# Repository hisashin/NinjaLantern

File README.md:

NinjaLantern
==========

Open Source(GPL) Transilluminator to view DNA,RNA,etc.

STL https://github.com/hisashin/NinjaLantern/blob/master/cad/3d/Illuminator_ver2.stl

Photos https://www.facebook.com/hisakawa/media_set?set=a.10151899171609481&type=3

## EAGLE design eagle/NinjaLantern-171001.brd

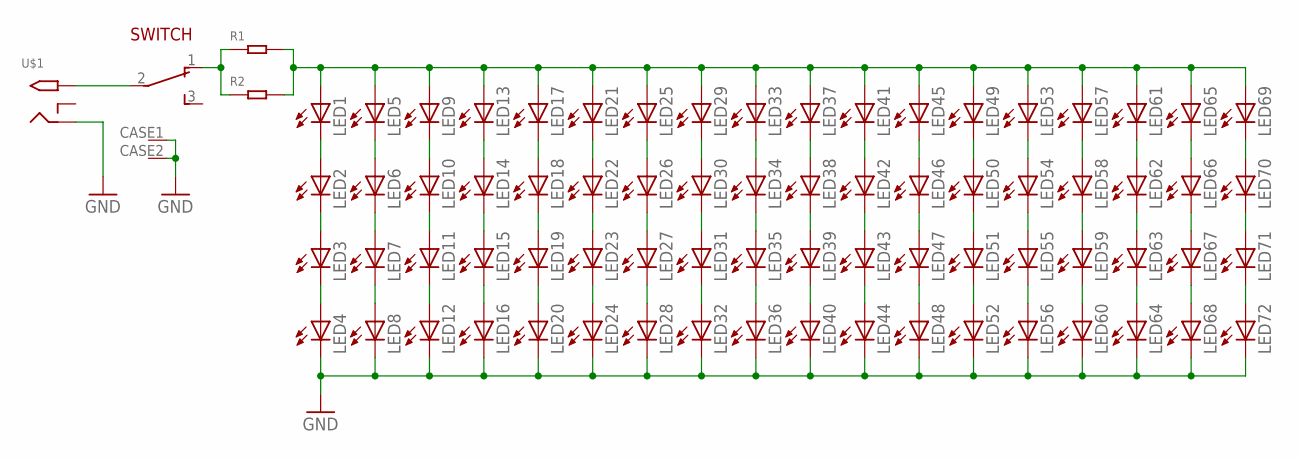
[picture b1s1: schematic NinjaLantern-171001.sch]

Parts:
LED1, LED2, LED3, LED4, LED5, LED6, LED7, LED8, LED9, LED10, LED11, LED12, LED13, LED14, LED15, LED16, LED17, LED18, LED19, LED20, LED21, LED22, LED23, LED24, LED25, LED26, LED27, LED28, LED29, LED30, LED31, LED32, LED33, LED34, LED35, LED36, LED37, LED38, LED39, LED40, LED41, LED42, LED43, LED44, LED45, LED46, LED47, LED48, LED49, LED50, LED51, LED52, LED53, LED54, LED55, LED56, LED57, LED58, LED59, LED60, LED61, LED62, LED63, LED64, LED65, LED66, LED67, LED68, LED69, LED70, LED71, LED72: LED5MM
R1, R2: DIP-RES-100R-5%-1/4W(PR-D2.3XL6.5MM); PR-D2.3XL6.5MM
SWITCH: 4MS1R202M6QES
U$1: 2.1MMJACKTHM; PJ-102A

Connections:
GND: LED4.K (C), LED8.K (C), LED12.K (C), LED16.K (C), LED20.K (C), LED24.K (C), LED28.K (C), LED32.K (C), LED36.K (C), LED40.K (C), LED44.K (C), LED48.K (C), LED52.K (C), LED56.K (C), LED60.K (C), LED64.K (C), LED68.K (C), LED72.K (C), U$1.RING
unnamed: LED3.K (C), LED4.A
unnamed: LED2.K (C), LED3.A
unnamed: LED1.K (C), LED2.A
unnamed: SWITCH.2, U$1.TIP
unnamed: LED7.K (C), LED8.A
unnamed: LED6.K (C), LED7.A
unnamed: LED5.K (C), LED6.A
unnamed: R1.1, R2.1, SWITCH.1
unnamed: LED1.A, LED5.A, LED9.A, LED13.A, LED17.A, LED21.A, LED25.A, LED29.A, LED33.A, LED37.A, LED41.A, LED45.A, LED49.A, LED53.A, LED57.A, LED61.A, LED65.A, LED69.A, R1.2, R2.2
unnamed: LED11.K (C), LED12.A
unnamed: LED10.K (C), LED11.A
unnamed: LED9.K (C), LED10.A
unnamed: LED15.K (C), LED16.A
unnamed: LED14.K (C), LED15.A
unnamed: LED13.K (C), LED14.A
unnamed: LED19.K (C), LED20.A
unnamed: LED18.K (C), LED19.A
unnamed: LED17.K (C), LED18.A
unnamed: LED23.K (C), LED24.A
unnamed: LED22.K (C), LED23.A
unnamed: LED21.K (C), LED22.A
unnamed: LED27.K (C), LED28.A
unnamed: LED26.K (C), LED27.A
unnamed: LED25.K (C), LED26.A
unnamed: LED31.K (C), LED32.A
unnamed: LED30.K (C), LED31.A
unnamed: LED29.K (C), LED30.A
unnamed: LED35.K (C), LED36.A
unnamed: LED34.K (C), LED35.A
unnamed: LED33.K (C), LED34.A
unnamed: LED39.K (C), LED40.A
unnamed: LED38.K (C), LED39.A
unnamed: LED37.K (C), LED38.A
unnamed: LED43.K (C), LED44.A
unnamed: LED42.K (C), LED43.A
unnamed: LED41.K (C), LED42.A
unnamed: LED47.K (C), LED48.A
unnamed: LED46.K (C), LED47.A
unnamed: LED45.K (C), LED46.A
unnamed: LED51.K (C), LED52.A
unnamed: LED50.K (C), LED51.A
unnamed: LED49.K (C), LED50.A
unnamed: LED55.K (C), LED56.A
unnamed: LED54.K (C), LED55.A
unnamed: LED53.K (C), LED54.A
unnamed: LED59.K (C), LED60.A
unnamed: LED58.K (C), LED59.A
unnamed: LED57.K (C), LED58.A
unnamed: LED63.K (C), LED64.A
unnamed: LED62.K (C), LED63.A
unnamed: LED61.K (C), LED62.A
unnamed: LED67.K (C), LED68.A
unnamed: LED66.K (C), LED67.A
unnamed: LED65.K (C), LED66.A
unnamed: LED71.K (C), LED72.A
unnamed: LED70.K (C), LED71.A
unnamed: LED69.K (C), LED70.A

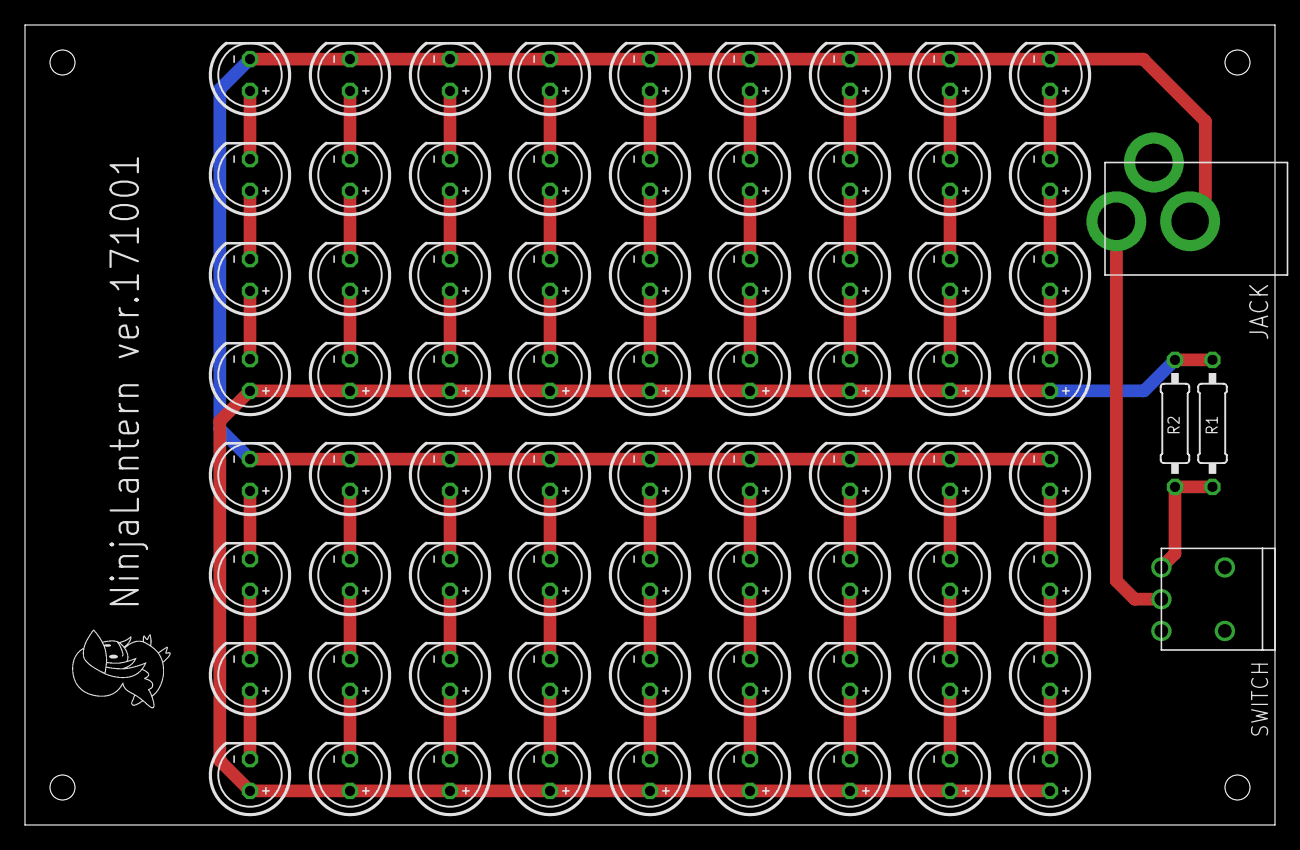
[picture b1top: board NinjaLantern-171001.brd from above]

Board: 2 copper layers, 100.0 x 64.0 mm, 77 parts (0 on the bottom side), 58 nets.

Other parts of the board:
U$2: TORI_0.25

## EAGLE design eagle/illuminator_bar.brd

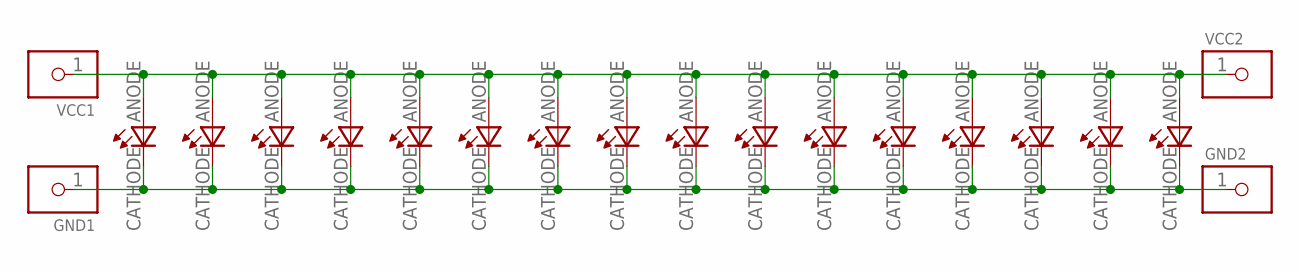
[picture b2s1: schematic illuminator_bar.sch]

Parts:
GND1, GND2: 1X0108L; 1X01_0.8_UNSIGNED_LONG
U$1, U$2, U$3, U$4, U$5, U$6, U$7, U$8, U$9, U$10, U$11, U$12, U$13, U$14, U$15, U$16: NSCB100
VCC1, VCC2: 1X0108L; 1X01_0.8_UNSIGNED_LONG

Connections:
GND: GND1.1, GND2.1, U$1.CATHODE (C), U$2.CATHODE (C), U$3.CATHODE (C), U$4.CATHODE (C), U$5.CATHODE (C), U$6.CATHODE (C), U$7.CATHODE (C), U$8.CATHODE (C), U$9.CATHODE (C), U$10.CATHODE (C), U$11.CATHODE (C), U$12.CATHODE (C), U$13.CATHODE (C), U$14.CATHODE (C), U$15.CATHODE (C), U$16.CATHODE (C)
VCC: U$1.ANODE (A), U$2.ANODE (A), U$3.ANODE (A), U$4.ANODE (A), U$5.ANODE (A), U$6.ANODE (A), U$7.ANODE (A), U$8.ANODE (A), U$9.ANODE (A), U$10.ANODE (A), U$11.ANODE (A), U$12.ANODE (A), U$13.ANODE (A), U$14.ANODE (A), U$15.ANODE (A), U$16.ANODE (A), VCC1.1, VCC2.1

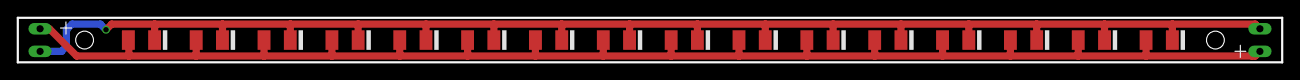
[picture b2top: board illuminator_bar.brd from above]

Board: 2 copper layers, 142.0 x 5.0 mm, 20 parts (0 on the bottom side), 2 nets.

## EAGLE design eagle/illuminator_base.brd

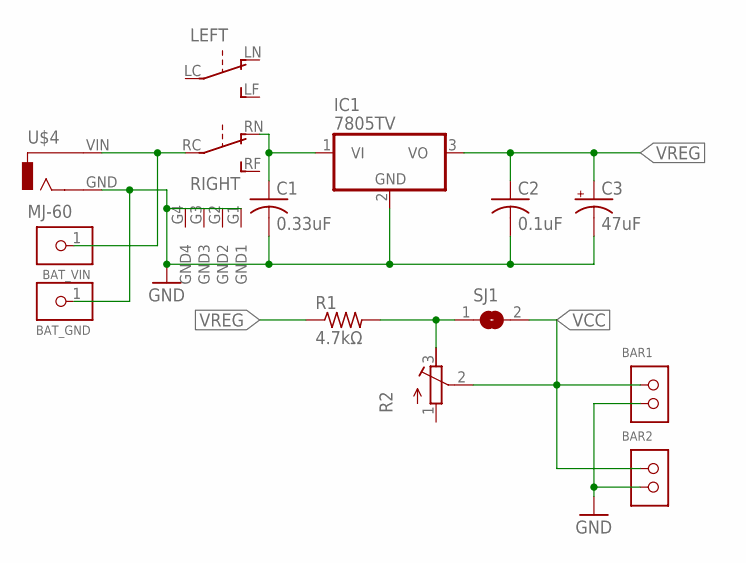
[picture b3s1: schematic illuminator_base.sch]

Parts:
BAR1, BAR2: 1X020.8L; 1X02_0.8_UNSIGNED_LONG
BAT_GND: 1X0108L; 1X01_0.8_UNSIGNED_LONG
BAT_VIN: 1X0108L; 1X01_0.8_UNSIGNED_LONG
C1: 0.33uF; C025-030X050
C2: 0.1uF; C025-030X050
C3: 47uF; E2-5
IC1: 7805TV; TO220V
R1: 4.7kΩ; 0204/7
R2: R-TRIMM3339P; RTRIM3339P
SJ1: SJ
U$3: M-2022NB
U$4: MJ-60

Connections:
GND: BAR1.2, BAR2.2, BAT_GND.1, C1.2, C2.2, C3.-, IC1.2 (GND), U$3.G1 (GND1), U$3.G2 (GND2), U$3.G3 (GND3), U$3.G4 (GND4), U$4.GND
unnamed: R1.2, R2.3 (A), SJ1.1
unnamed: C1.1, IC1.1 (VI), U$3.RN (RIGHT_ON)
VCC: BAR1.1, BAR2.1, R2.2 (S), SJ1.2
VIN: BAT_VIN.1, U$3.RC (RIGHT_CENTER), U$4.VIN
VREG: C2.1, C3.+, IC1.3 (VO), R1.1

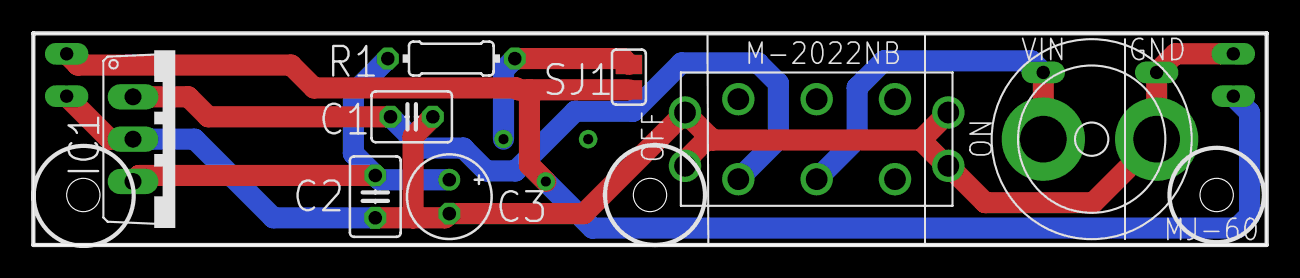
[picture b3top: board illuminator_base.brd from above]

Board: 2 copper layers, 74.0 x 12.7 mm, 13 parts (1 on the bottom side), 6 nets.

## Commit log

2013-10-11 added 3d models
2013-10-14 rename to NinjaLantern
2013-10-14 add eagle files
2013-10-14 add url of facebook album
2013-10-14 it's GPL!
2013-10-14 add logo
2014-02-03 Rebuild as ver2
2014-02-03 rename old broken one as ver1
2014-02-03 add link to STL
2014-02-03 add photo
2014-02-03 add br
2014-02-03 update olds
2017-10-03 add pcb
2017-10-09 ordered pcb
